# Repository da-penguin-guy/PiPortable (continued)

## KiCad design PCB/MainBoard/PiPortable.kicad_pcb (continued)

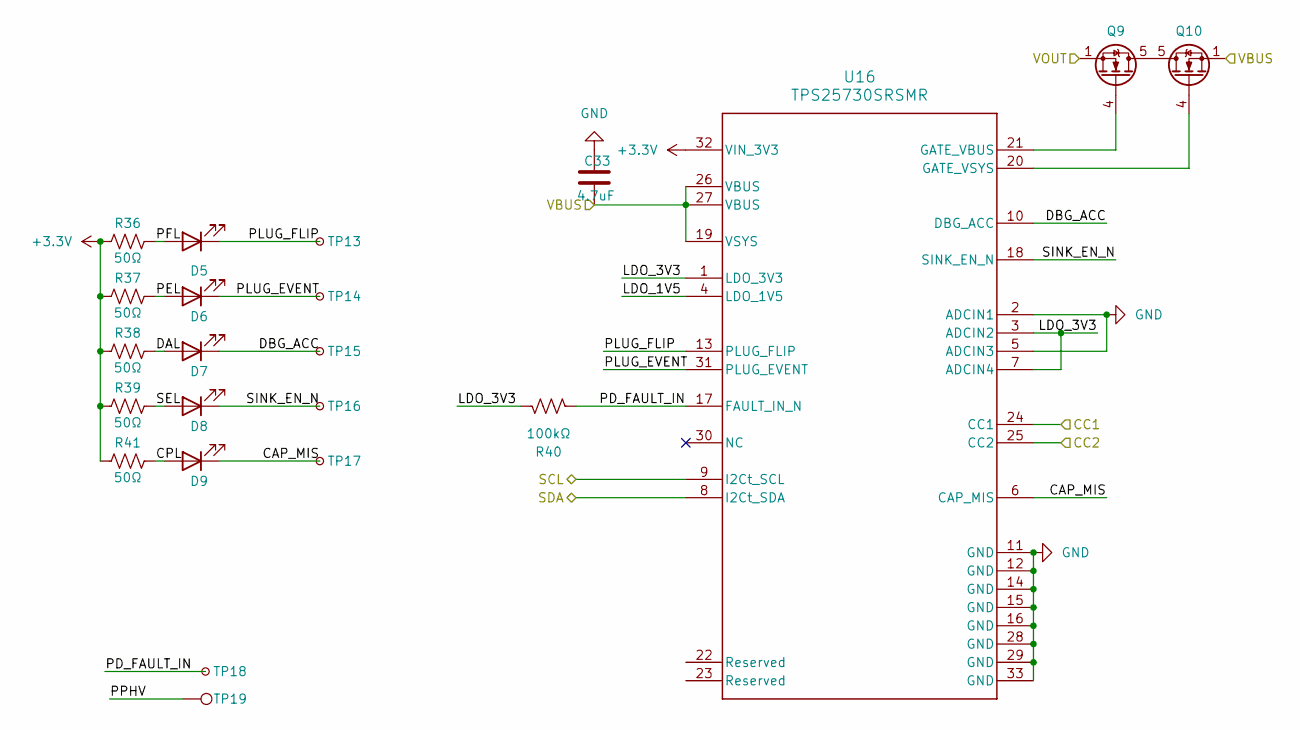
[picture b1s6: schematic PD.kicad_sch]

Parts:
C33: 4.7uF; C_0603_1608Metric_Pad1.08x0.95mm_HandSolder
D5, D6, D7, D8, D9: KT-0603R; LED_0603_1608Metric
Q9, Q10: CSD17577Q3A; VSON-8_3.3x3.3mm_P0.65mm_NexFET
R36, R37, R38, R39, R41: 50Ω; R_0402_1005Metric_Pad0.72x0.64mm_HandSolder
R40: 100kΩ; R_0402_1005Metric_Pad0.72x0.64mm_HandSolder
TP13, TP14, TP15, TP16, TP17, TP18: TestPoint_Small; TestPoint_Pad_D1.0mm
TP19: TestPoint; TestPoint_Pad_D3.0mm
U16: TPS25730SRSMR; RSM0032B-IPC_A

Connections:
+3.3V: R36.2, R37.2, R38.2, R39.2, R41.2, U16.32 (VIN_3V3); also elsewhere on the board
/PD Controller/CAP_MIS: D9.1 (K), TP17.1, U16.6 (CAP_MIS)
/PD Controller/CC1: U16.24 (CC1); also elsewhere on the board
/PD Controller/CC2: U16.25 (CC2); also elsewhere on the board
/PD Controller/CPL: D9.2 (A), R41.1
/PD Controller/DAL: D7.2 (A), R38.1
/PD Controller/DBG_ACC: D7.1 (K), TP15.1, U16.10 (DBG_ACC)
/PD Controller/LDO_1V5: U16.4 (LDO_1V5)
/PD Controller/LDO_3V3: R40.2, U16.1 (LDO_3V3), U16.3 (ADCIN2), U16.7 (ADCIN4)
/PD Controller/PD_FAULT_IN: R40.1, TP18.1, U16.17 (FAULT_IN_N)
/PD Controller/PEL: D6.2 (A), R37.1
/PD Controller/PFL: D5.2 (A), R36.1
/PD Controller/PLUG_EVENT: D6.1 (K), TP14.1, U16.31 (PLUG_EVENT)
/PD Controller/PLUG_FLIP: D5.1 (K), TP13.1, U16.13 (PLUG_FLIP)
/PD Controller/PPHV: TP19.1
/PD Controller/SEL: D8.2 (A), R39.1
/PD Controller/SINK_EN_N: D8.1 (K), TP16.1, U16.18 (SINK_EN_N)
/PD Controller/VOUT: Q9.1 (S), Q9.2 (S), Q9.3 (S); also elsewhere on the board
/SCL_INT: U16.9 (I2Ct_SCL); also elsewhere on the board
/SDA_INT: U16.8 (I2Ct_SDA); also elsewhere on the board
/VBUS: C33.2, Q10.1 (S), Q10.2 (S), Q10.3 (S), U16.19 (VSYS), U16.26 (VBUS), U16.27 (VBUS); also elsewhere on the board
GND: C33.1, U16.2 (ADCIN1), U16.5 (ADCIN3), U16.11 (GND), U16.12 (GND), U16.14 (GND), U16.15 (GND), U16.16 (GND), U16.28 (GND), U16.29 (GND), U16.33 (GND); also elsewhere on the board
unnamed: Q9.4 (G), U16.21 (GATE_VBUS)
unnamed: Q9.5 (D), Q10.5 (D)
unnamed: Q10.4 (G), U16.20 (GATE_VSYS)

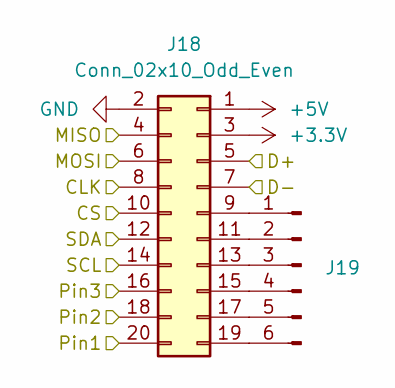
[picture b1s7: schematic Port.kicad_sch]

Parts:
J18: Conn_02x10_Odd_Even; PinSocket_2x10_P2.00mm_Horizontal
J19: Conn_01x06_Pin; PinHeader_1x06_P1.27mm_Vertical

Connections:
+3.3V: J18.3; also elsewhere on the board
+5V: J18.1; also elsewhere on the board
/CM5_GPIO ( Ethernet, GPIO, SDCARD)/GPIO9: J18.4; also elsewhere on the board
/CM5_GPIO ( Ethernet, GPIO, SDCARD)/GPIO10: J18.6; also elsewhere on the board
/CM5_GPIO ( Ethernet, GPIO, SDCARD)/GPIO11: J18.8; also elsewhere on the board
/CM5_GPIO ( Ethernet, GPIO, SDCARD)/GPIO22: J18.10; also elsewhere on the board
/IO Ports/Port1/D+: J18.5; also elsewhere on the board
/IO Ports/Port1/D-: J18.7; also elsewhere on the board
/IO Ports/Port1P1: J18.20; also elsewhere on the board
/IO Ports/Port1P2: J18.18; also elsewhere on the board
/IO Ports/Port1P3: J18.16; also elsewhere on the board
/SCL_GPIO: J18.14; also elsewhere on the board
/SDA_GPIO: J18.12; also elsewhere on the board
GND: J18.2; also elsewhere on the board
unnamed: J18.9, J19.1
unnamed: J18.11, J19.2
unnamed: J18.13, J19.3
unnamed: J18.15, J19.4
unnamed: J18.17, J19.5
unnamed: J18.19, J19.6

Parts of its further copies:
J20, J22, J24: Conn_02x10_Odd_Even; PinSocket_2x10_P2.00mm_Horizontal
J21, J23, J25: Conn_01x06_Pin; PinHeader_1x06_P1.27mm_Vertical

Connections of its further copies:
+3.3V: J20.3, J22.3, J24.3; also elsewhere on the board
+5V: J20.1, J22.1, J24.1; also elsewhere on the board
/CM5_GPIO ( Ethernet, GPIO, SDCARD)/GPIO9: J20.4, J22.4, J24.4; also elsewhere on the board
/CM5_GPIO ( Ethernet, GPIO, SDCARD)/GPIO10: J20.6, J22.6, J24.6; also elsewhere on the board
/CM5_GPIO ( Ethernet, GPIO, SDCARD)/GPIO11: J20.8, J22.8, J24.8; also elsewhere on the board
/CM5_GPIO ( Ethernet, GPIO, SDCARD)/GPIO23: J20.10; also elsewhere on the board
/CM5_GPIO ( Ethernet, GPIO, SDCARD)/GPIO24: J22.10; also elsewhere on the board
/CM5_GPIO ( Ethernet, GPIO, SDCARD)/GPIO25: J24.10; also elsewhere on the board
/IO Ports/Port2/D+: J20.5; also elsewhere on the board
/IO Ports/Port2/D-: J20.7; also elsewhere on the board
/IO Ports/Port2P1: J20.20; also elsewhere on the board
/IO Ports/Port2P2: J20.18; also elsewhere on the board
/IO Ports/Port2P3: J20.16; also elsewhere on the board
/IO Ports/Port3/D+: J22.5; also elsewhere on the board
/IO Ports/Port3/D-: J22.7; also elsewhere on the board
/IO Ports/Port3P1: J22.20; also elsewhere on the board
/IO Ports/Port3P2: J22.18; also elsewhere on the board
/IO Ports/Port3P3: J22.16; also elsewhere on the board
/IO Ports/Port4/D+: J24.5; also elsewhere on the board
/IO Ports/Port4/D-: J24.7; also elsewhere on the board
/IO Ports/Port4P1: J24.20; also elsewhere on the board
/IO Ports/Port4P2: J24.18; also elsewhere on the board
/IO Ports/Port4P3: J24.16; also elsewhere on the board
/SCL_GPIO: J20.14, J22.14, J24.14; also elsewhere on the board
/SDA_GPIO: J20.12, J22.12, J24.12; also elsewhere on the board
GND: J20.2, J22.2, J24.2; also elsewhere on the board
unnamed: J20.9, J21.1
unnamed: J20.11, J21.2
unnamed: J20.13, J21.3
unnamed: J20.15, J21.4
unnamed: J20.17, J21.5
unnamed: J20.19, J21.6
unnamed: J22.9, J23.1
unnamed: J22.11, J23.2
unnamed: J22.13, J23.3
unnamed: J22.15, J23.4
unnamed: J22.17, J23.5
unnamed: J22.19, J23.6
unnamed: J24.9, J25.1
unnamed: J24.11, J25.2
unnamed: J24.13, J25.3
unnamed: J24.15, J25.4
unnamed: J24.17, J25.5
unnamed: J24.19, J25.6

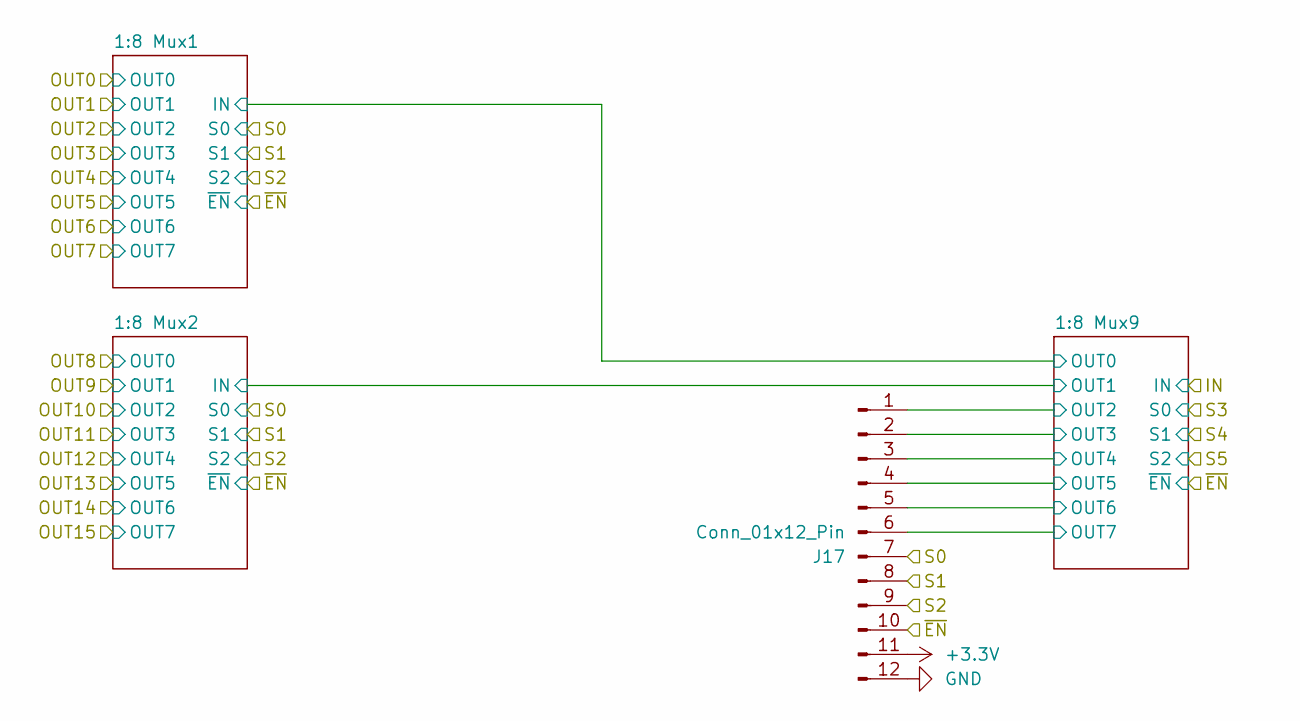
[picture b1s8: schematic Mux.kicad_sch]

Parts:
J17: Conn_01x12_Pin; PinHeader_1x12_P1.27mm_Vertical

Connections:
+3.3V: J17.11; also elsewhere on the board
/IO Ports/Mux 2/1:8 Mux9/OUT2: J17.1; also elsewhere on the board
/IO Ports/Mux 2/1:8 Mux9/OUT3: J17.2; also elsewhere on the board
/IO Ports/Mux 2/1:8 Mux9/OUT4: J17.3; also elsewhere on the board
/IO Ports/Mux 2/1:8 Mux9/OUT5: J17.4; also elsewhere on the board
/IO Ports/Mux 2/1:8 Mux9/OUT6: J17.5; also elsewhere on the board
/IO Ports/Mux 2/1:8 Mux9/OUT7: J17.6; also elsewhere on the board
/IO Ports/Mux 2/S0: J17.7; also elsewhere on the board
/IO Ports/Mux 2/S1: J17.8; also elsewhere on the board
/IO Ports/Mux 2/S2: J17.9; also elsewhere on the board
/IO Ports/Mux 2/~EN: J17.10; also elsewhere on the board
GND: J17.12; also elsewhere on the board

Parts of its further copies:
J16: Conn_01x12_Pin; PinHeader_1x12_P1.27mm_Vertical

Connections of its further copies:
+3.3V: J16.11; also elsewhere on the board
/IO Ports/Mux 1/1:8 Mux9/OUT2: J16.1; also elsewhere on the board
/IO Ports/Mux 1/1:8 Mux9/OUT3: J16.2; also elsewhere on the board
/IO Ports/Mux 1/1:8 Mux9/OUT4: J16.3; also elsewhere on the board
/IO Ports/Mux 1/1:8 Mux9/OUT5: J16.4; also elsewhere on the board
/IO Ports/Mux 1/1:8 Mux9/OUT6: J16.5; also elsewhere on the board
/IO Ports/Mux 1/1:8 Mux9/OUT7: J16.6; also elsewhere on the board
/IO Ports/Mux 1/S0: J16.7; also elsewhere on the board
/IO Ports/Mux 1/S1: J16.8; also elsewhere on the board
/IO Ports/Mux 1/S2: J16.9; also elsewhere on the board
/IO Ports/Mux 1/~EN: J16.10; also elsewhere on the board
GND: J16.12; also elsewhere on the board

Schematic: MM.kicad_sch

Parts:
J15: Conn_01x02_Pin; PinHeader_1x02_P1.27mm_Vertical
Q1, Q2: 2N7002; SOT-23
R7: 50Ω; R_0402_1005Metric_Pad0.72x0.64mm_HandSolder
U4: PINA780BIDEKR; VQFN15_DEK_TEX

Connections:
+3.3V: Q1.2 (S), U4.15 (IS+); also elsewhere on the board
/IO Ports/Multimeter/3.3EN: Q1.1 (G); also elsewhere on the board
/IO Ports/Multimeter/GNDEN: Q2.1 (G); also elsewhere on the board
/IO Ports/VS+: J15.1, R7.2, U4.6 (SCL), U4.7 (NC); also elsewhere on the board
/IO Ports/VS-: Q2.3 (D); also elsewhere on the board
/SCL_GPIO: U4.10 (IN-); also elsewhere on the board
/SDA_GPIO: U4.11 (ALERT); also elsewhere on the board
GND: Q2.2 (S); also elsewhere on the board
unnamed: J15.2, Q1.3 (D), R7.1

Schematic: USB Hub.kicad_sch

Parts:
R8: 12kΩ; R_0402_1005Metric_Pad0.72x0.64mm_HandSolder
TP2, TP3, TP4, TP5: TestPoint_Small; TestPoint_Pad_D1.0mm
U5: USB2514B_Bi; QFN-36-1EP_6x6mm_P0.5mm_EP3.7x3.7mm
Y1: ABM8-24.000MHZ-D1G-T; Crystal_SMD_Abracon_ABM8G-4Pin_3.2x2.5mm

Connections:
+3.3V: U5.5 (VDDA33), U5.10 (VDDA33), U5.15 (VDD33), U5.23 (VDD33), U5.26 (RESET_N), U5.27 (VBUS_DET), U5.29 (VDDA33), U5.36 (VDDA33); also elsewhere on the board
/CM5_HighSpeed/USB3-1-D_N: U5.30 (USBDM_UP); also elsewhere on the board
/CM5_HighSpeed/USB3-1-D_P: U5.31 (USBDP_UP); also elsewhere on the board
/IO Ports/Port1/D+: U5.2 (USBDP_DN1/PRT_DIS_P1); also elsewhere on the board
/IO Ports/Port1/D-: U5.1 (USBDM_DN1/PRT_DIS_M1); also elsewhere on the board
/IO Ports/Port2/D+: U5.4 (USBDP_DN2/PRT_DIS_P2); also elsewhere on the board
/IO Ports/Port2/D-: U5.3 (USBDM_DN2/PRT_DIS_M2); also elsewhere on the board
/IO Ports/Port3/D+: U5.7 (USBDP_DN3/PRT_DIS_P3); also elsewhere on the board
/IO Ports/Port3/D-: U5.6 (USBDM_DN3/PRT_DIS_M3); also elsewhere on the board
/IO Ports/Port4/D+: U5.9 (USBDP_DN4/PRT_DIS_P4); also elsewhere on the board
/IO Ports/Port4/D-: U5.8 (USBDM_DN4/PRT_DIS_M4); also elsewhere on the board
/SCL_GPIO: U5.24 (SCL/SMBCLK/CFG_SEL0); also elsewhere on the board
/SDA_GPIO: U5.22 (SDA/SMBDATA/NON_REM1); also elsewhere on the board
GND: R8.1, U5.12 (PRTPWR1/BC_EN1), U5.16 (PRTPWR2/BC_EN2), U5.18 (PRTPWR3/BC_EN3), U5.20 (PRTPWR4/BC_EN4), U5.37 (VSS), Y1.2, Y1.4; also elsewhere on the board
unnamed: TP2.1, U5.13 (OCS_N1)
unnamed: TP3.1, U5.17 (OCS_N2)
unnamed: TP4.1, U5.19 (OCS_N3)
unnamed: TP5.1, U5.21 (OCS_N4)
unnamed: R8.2, U5.35 (RBIAS)
unnamed: U5.33 (XTALIN/CLKIN), Y1.1
unnamed: U5.32 (XTALOUT), Y1.3

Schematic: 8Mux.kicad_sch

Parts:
U10: 74HC4051; TSSOP-16_4.4x5mm_P0.65mm

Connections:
+3.3V: U10.16 (VCC); also elsewhere on the board
/IO Ports/L12: U10.1 (A4); also elsewhere on the board
/IO Ports/L13: U10.5 (A5); also elsewhere on the board
/IO Ports/L14: U10.2 (A6); also elsewhere on the board
/IO Ports/L15: U10.4 (A7); also elsewhere on the board
/IO Ports/Mux 2/1:8 Mux2/IN: U10.3 (A); also elsewhere on the board
/IO Ports/Mux 2/S0: U10.11 (S0); also elsewhere on the board
/IO Ports/Mux 2/S1: U10.10 (S1); also elsewhere on the board
/IO Ports/Mux 2/S2: U10.9 (S2); also elsewhere on the board
/IO Ports/Mux 2/~EN: U10.6 (~E); also elsewhere on the board
/IO Ports/Port3P3: U10.13 (A0); also elsewhere on the board
/IO Ports/Port4P1: U10.14 (A1); also elsewhere on the board
/IO Ports/Port4P2: U10.15 (A2); also elsewhere on the board
/IO Ports/Port4P3: U10.12 (A3); also elsewhere on the board
GND: U10.7 (VEE), U10.8 (GND); also elsewhere on the board

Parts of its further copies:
U7, U8, U9, U11, U13: 74HC4051; TSSOP-16_4.4x5mm_P0.65mm

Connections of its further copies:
+3.3V: U7.16 (VCC), U8.16 (VCC), U9.16 (VCC), U11.16 (VCC), U13.16 (VCC); also elsewhere on the board
/IO Ports/H12: U7.1 (A4); also elsewhere on the board
/IO Ports/H13: U7.5 (A5); also elsewhere on the board
/IO Ports/H14: U7.2 (A6); also elsewhere on the board
/IO Ports/H15: U7.4 (A7); also elsewhere on the board
/IO Ports/Mux 1/1:8 Mux1/IN: U8.3 (A), U13.13 (A0)
/IO Ports/Mux 1/1:8 Mux2/IN: U7.3 (A), U13.14 (A1)
/IO Ports/Mux 1/1:8 Mux9/OUT2: U13.15 (A2); also elsewhere on the board
/IO Ports/Mux 1/1:8 Mux9/OUT3: U13.12 (A3); also elsewhere on the board
/IO Ports/Mux 1/1:8 Mux9/OUT4: U13.1 (A4); also elsewhere on the board
/IO Ports/Mux 1/1:8 Mux9/OUT5: U13.5 (A5); also elsewhere on the board
/IO Ports/Mux 1/1:8 Mux9/OUT6: U13.2 (A6); also elsewhere on the board
/IO Ports/Mux 1/1:8 Mux9/OUT7: U13.4 (A7); also elsewhere on the board
/IO Ports/Mux 1/S0: U7.11 (S0), U8.11 (S0); also elsewhere on the board
/IO Ports/Mux 1/S1: U7.10 (S1), U8.10 (S1); also elsewhere on the board
/IO Ports/Mux 1/S2: U7.9 (S2), U8.9 (S2); also elsewhere on the board
/IO Ports/Mux 1/S3: U13.11 (S0); also elsewhere on the board
/IO Ports/Mux 1/S4: U13.10 (S1); also elsewhere on the board
/IO Ports/Mux 1/S5: U13.9 (S2); also elsewhere on the board
/IO Ports/Mux 1/~EN: U7.6 (~E), U8.6 (~E), U13.6 (~E); also elsewhere on the board
/IO Ports/Mux 2/1:8 Mux1/IN: U9.13 (A0), U11.3 (A)
/IO Ports/Mux 2/1:8 Mux2/IN: U9.14 (A1); also elsewhere on the board
/IO Ports/Mux 2/1:8 Mux9/OUT2: U9.15 (A2); also elsewhere on the board
/IO Ports/Mux 2/1:8 Mux9/OUT3: U9.12 (A3); also elsewhere on the board
/IO Ports/Mux 2/1:8 Mux9/OUT4: U9.1 (A4); also elsewhere on the board
/IO Ports/Mux 2/1:8 Mux9/OUT5: U9.5 (A5); also elsewhere on the board
/IO Ports/Mux 2/1:8 Mux9/OUT6: U9.2 (A6); also elsewhere on the board
/IO Ports/Mux 2/1:8 Mux9/OUT7: U9.4 (A7); also elsewhere on the board
/IO Ports/Mux 2/S0: U11.11 (S0); also elsewhere on the board
/IO Ports/Mux 2/S1: U11.10 (S1); also elsewhere on the board
/IO Ports/Mux 2/S2: U11.9 (S2); also elsewhere on the board
/IO Ports/Mux 2/S3: U9.11 (S0); also elsewhere on the board
/IO Ports/Mux 2/S4: U9.10 (S1); also elsewhere on the board
/IO Ports/Mux 2/S5: U9.9 (S2); also elsewhere on the board
/IO Ports/Mux 2/~EN: U9.6 (~E), U11.6 (~E); also elsewhere on the board
/IO Ports/Port1P1: U8.13 (A0), U11.13 (A0); also elsewhere on the board
/IO Ports/Port1P2: U8.14 (A1), U11.14 (A1); also elsewhere on the board
/IO Ports/Port1P3: U8.15 (A2), U11.15 (A2); also elsewhere on the board
/IO Ports/Port2P1: U8.12 (A3), U11.12 (A3); also elsewhere on the board
/IO Ports/Port2P2: U8.1 (A4), U11.1 (A4); also elsewhere on the board
/IO Ports/Port2P3: U8.5 (A5), U11.5 (A5); also elsewhere on the board
/IO Ports/Port3P1: U8.2 (A6), U11.2 (A6); also elsewhere on the board
/IO Ports/Port3P2: U8.4 (A7), U11.4 (A7); also elsewhere on the board
/IO Ports/Port3P3: U7.13 (A0); also elsewhere on the board
/IO Ports/Port4P1: U7.14 (A1); also elsewhere on the board
/IO Ports/Port4P2: U7.15 (A2); also elsewhere on the board
/IO Ports/Port4P3: U7.12 (A3); also elsewhere on the board
/IO Ports/VS+: U13.3 (A); also elsewhere on the board
/IO Ports/VS-: U9.3 (A); also elsewhere on the board
GND: U7.7 (VEE), U7.8 (GND), U8.7 (VEE), U8.8 (GND), U9.7 (VEE), U9.8 (GND), U11.7 (VEE), U11.8 (GND), U13.7 (VEE), U13.8 (GND); also elsewhere on the board

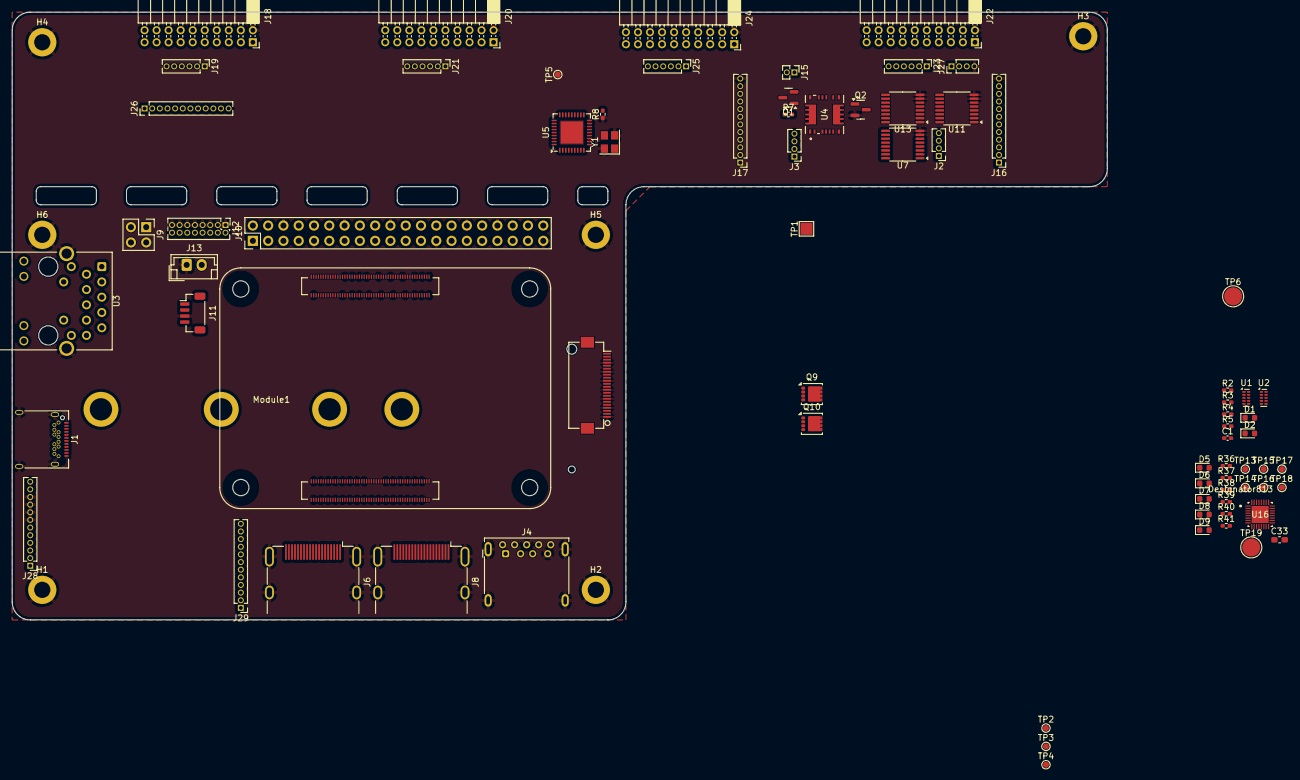
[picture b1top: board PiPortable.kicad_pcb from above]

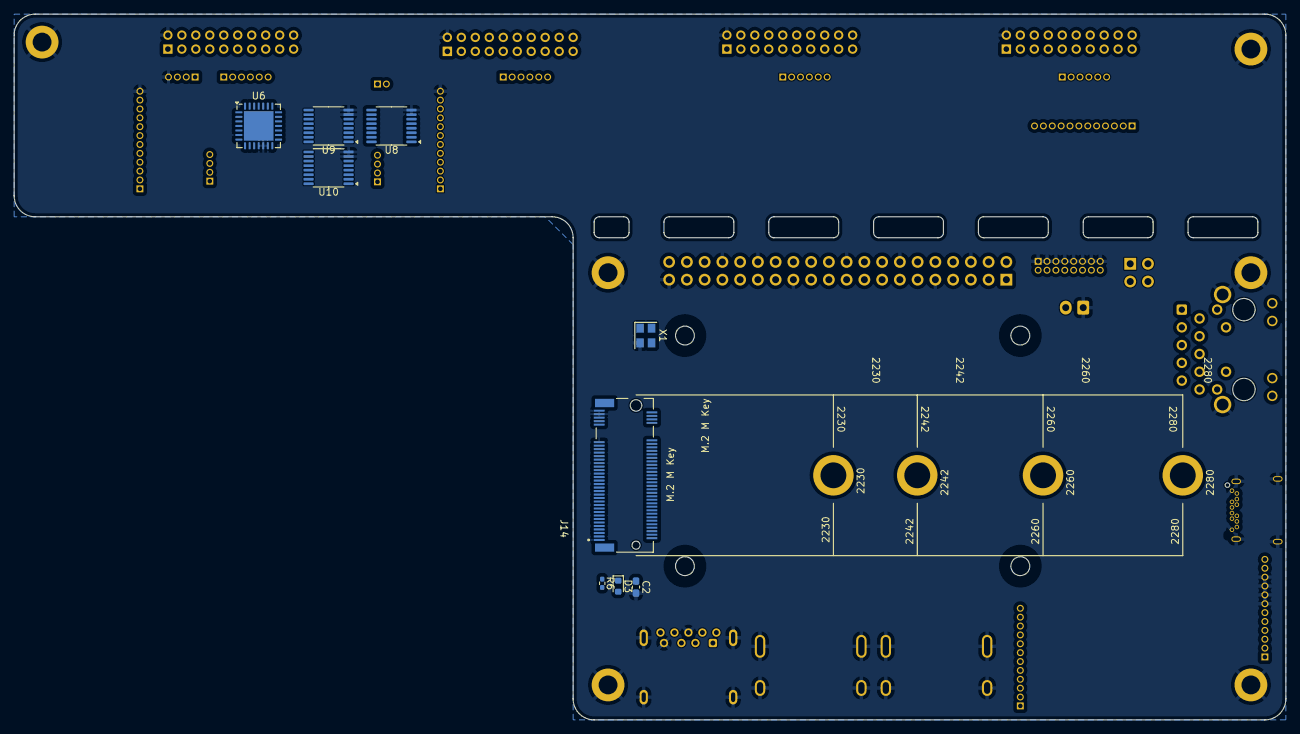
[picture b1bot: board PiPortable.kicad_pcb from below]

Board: 6 copper layers, 182.0 x 101.0 mm, 91 parts (9 on the bottom side), 238 nets.

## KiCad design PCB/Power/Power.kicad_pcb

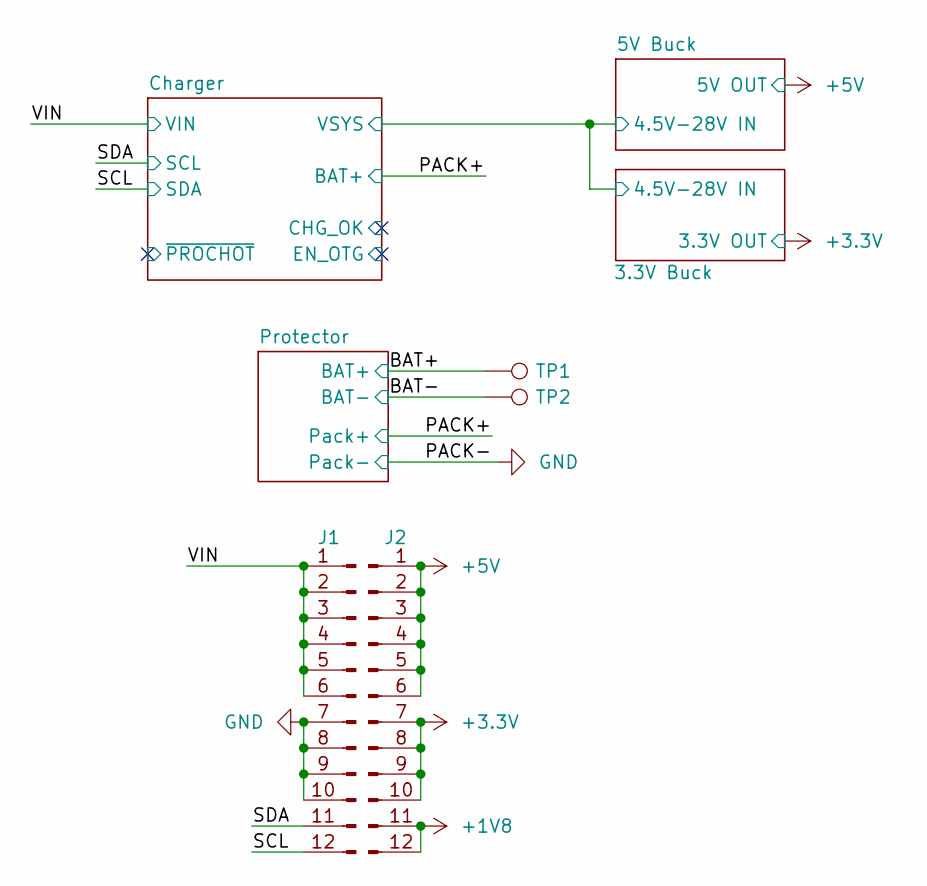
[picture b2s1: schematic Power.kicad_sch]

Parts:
J1, J2: Conn_01x12_Pin; PinSocket_1x12_P1.27mm_Vertical
TP1, TP2: TestPoint; TestPoint_THTPad_D3.0mm_Drill1.5mm

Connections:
+1V8: J2.11, J2.12
+3.3V: J2.7, J2.8, J2.9, J2.10; also elsewhere on the board
+5V: J2.1, J2.2, J2.3, J2.4, J2.5, J2.6; also elsewhere on the board
/BAT+: TP1.1; also elsewhere on the board
/BAT-: TP2.1; also elsewhere on the board
/SCL: J1.12; also elsewhere on the board
/SDA: J1.11; also elsewhere on the board
/VIN: J1.1, J1.2, J1.3, J1.4, J1.5, J1.6; also elsewhere on the board
GND: J1.7, J1.8, J1.9, J1.10; also elsewhere on the board

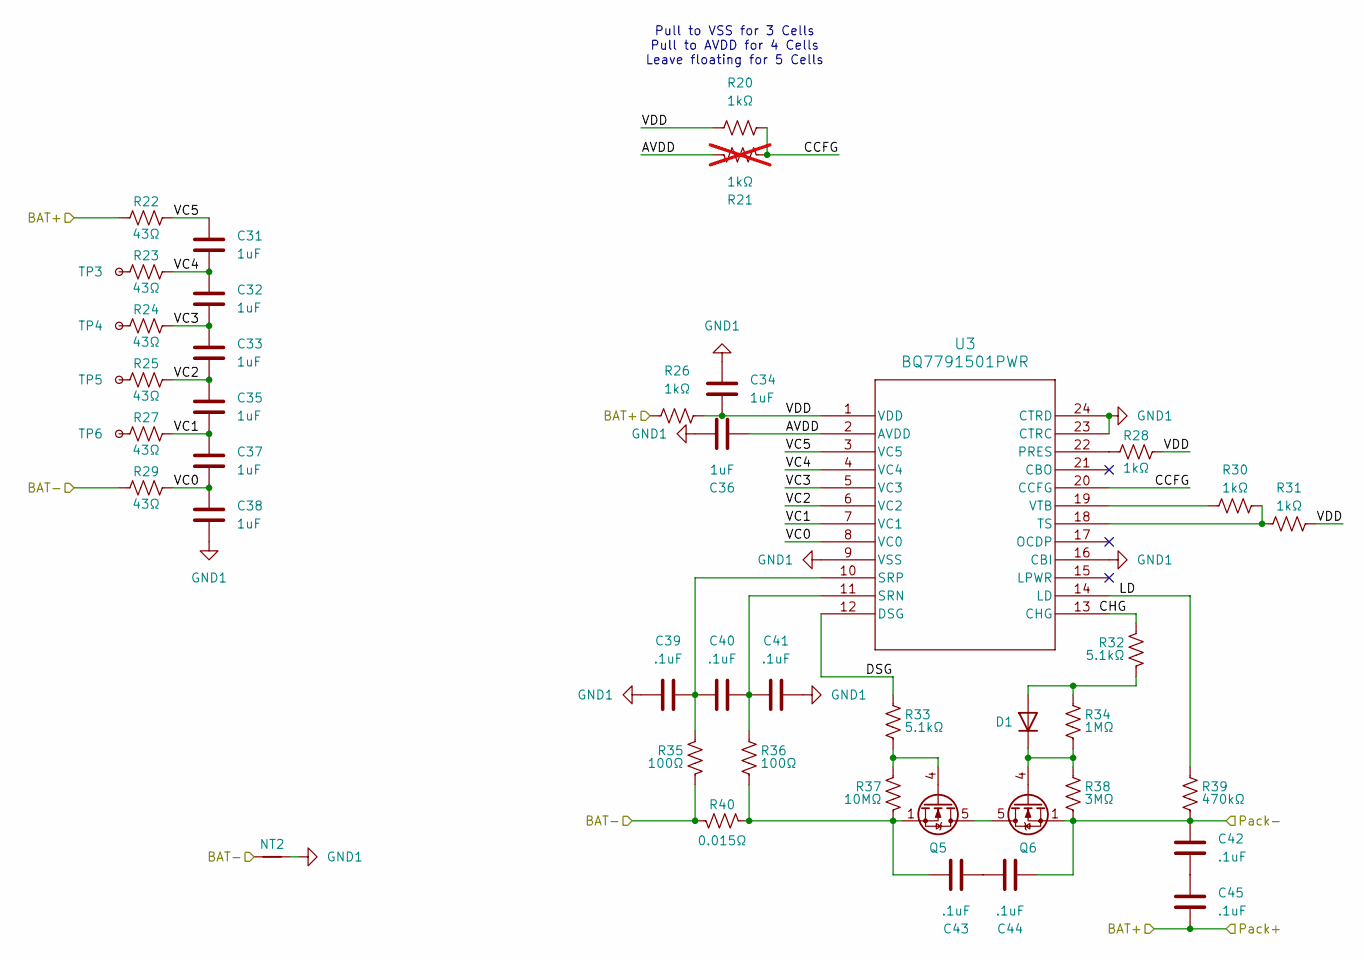
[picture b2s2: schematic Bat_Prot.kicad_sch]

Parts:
C31, C32, C33, C34, C35, C36, C37, C38: 1uF; C_0402_1005Metric_Pad0.74x0.62mm_HandSolder
C39, C40, C41, C42, C43, C44, C45: .1uF; C_0402_1005Metric_Pad0.74x0.62mm_HandSolder
D1: BAS16J,135; D_SOD-323F
NT2: NetTie_2; NetTie-2_SMD_Pad2.0mm
Q5, Q6: CSD17577Q3A; VSON-8_3.3x3.3mm_P0.65mm_NexFET
R20, R26, R28, R30, R31: 1kΩ; R_0402_1005Metric_Pad0.72x0.64mm_HandSolder
R21: 1kΩ; R_0402_1005Metric_Pad0.72x0.64mm_HandSolder; not fitted
R22, R23, R24, R25, R27, R29: 43Ω; R_0402_1005Metric_Pad0.72x0.64mm_HandSolder
R32, R33: 5.1kΩ; R_0402_1005Metric_Pad0.72x0.64mm_HandSolder
R34: 1MΩ; R_0603_1608Metric_Pad0.98x0.95mm_HandSolder
R35, R36: 100Ω; R_0402_1005Metric_Pad0.72x0.64mm_HandSolder
R37: 10MΩ; R_0603_1608Metric_Pad0.98x0.95mm_HandSolder
R38: 3MΩ; R_0603_1608Metric_Pad0.98x0.95mm_HandSolder
R39: 470kΩ; R_0402_1005Metric_Pad0.72x0.64mm_HandSolder
R40: 0.015Ω; R_0805_2012Metric_Pad1.20x1.40mm_HandSolder
TP3, TP4, TP5, TP6: TestPoint_Small; TestPoint_Pad_D1.0mm
U3: BQ7791501PWR; PW24_TEX

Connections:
/BAT+: C45.2, R22.1, R26.1; also elsewhere on the board
/BAT-: NT2.1, R29.1, R35.2, R40.2; also elsewhere on the board
/Protector/AVDD: C36.2, R21.2, U3.2 (AVDD)
/Protector/CCFG: R20.2, R21.1, U3.20 (CCFG)
/Protector/CHG: R32.1, U3.13 (CHG)
/Protector/DSG: R33.1, U3.12 (DSG)
/Protector/LD: R39.1, U3.14 (LD)
/Protector/VC0: C37.2, C38.1, R29.2, U3.8 (VC0)
/Protector/VC1: C35.2, C37.1, R27.2, U3.7 (VC1)
/Protector/VC2: C33.2, C35.1, R25.2, U3.6 (VC2)
/Protector/VC3: C32.2, C33.1, R24.2, U3.5 (VC3)
/Protector/VC4: C31.2, C32.1, R23.2, U3.4 (VC4)
/Protector/VC5: C31.1, R22.2, U3.3 (VC5)
/Protector/VDD: C34.2, R20.1, R26.2, R28.2, R31.2, U3.1 (VDD)
GND: C42.1, C44.2, Q6.1 (S), Q6.2 (S), Q6.3 (S), R38.2, R39.2; also elsewhere on the board
GND1: C34.1, C36.1, C38.2, C39.2, C41.2, NT2.2, U3.9 (VSS), U3.16 (CBI), U3.23 (CTRC), U3.24 (CTRD)
unnamed: C42.2, C45.1
unnamed: C43.1, Q5.1 (S), Q5.2 (S), Q5.3 (S), R36.2, R37.2, R40.1
unnamed: C43.2, C44.1
unnamed: D1.2 (A), R32.2, R34.1
unnamed: D1.1 (K), Q6.4 (G), R34.2, R38.1
unnamed: Q5.5 (D), Q6.5 (D)
unnamed: Q5.4 (G), R33.2, R37.1
unnamed: R23.1, TP3.1
unnamed: R24.1, TP4.1
unnamed: R25.1, TP5.1
unnamed: R27.1, TP6.1
unnamed: R28.1, U3.22 (PRES)
unnamed: C40.2, C41.1, R36.1, U3.11 (SRN)
unnamed: C39.1, C40.1, R35.1, U3.10 (SRP)
unnamed: R30.2, R31.1, U3.18 (TS)
unnamed: R30.1, U3.19 (VTB)

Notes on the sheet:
Pull to VSS for 3 Cells Pull to AVDD for 4 Cells Leave floating for 5 Cells

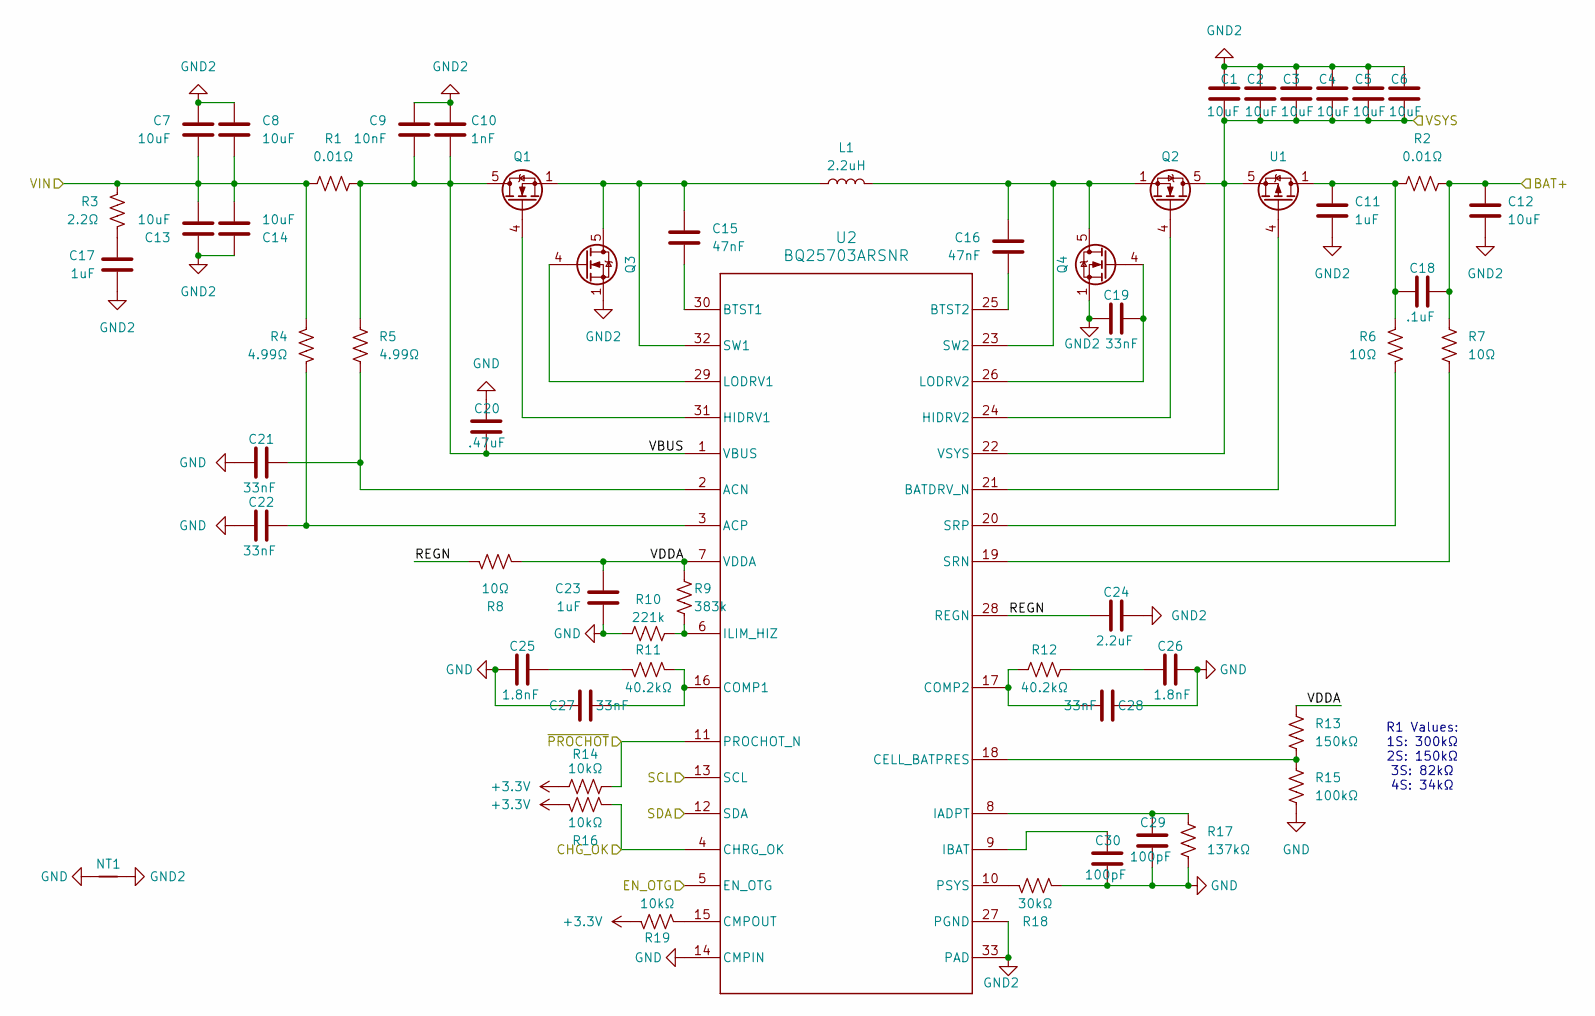
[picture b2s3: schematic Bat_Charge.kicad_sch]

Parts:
C1, C2, C3, C4, C7, C8, C12, C13, C14: 10uF; C_0603_1608Metric_Pad1.08x0.95mm_HandSolder
C5, C6: 10uF; C_0402_1005Metric_Pad0.74x0.62mm_HandSolder
C9: 10nF; C_0402_1005Metric_Pad0.74x0.62mm_HandSolder
C10: 1nF; C_0402_1005Metric_Pad0.74x0.62mm_HandSolder
C11: 1uF; C_0603_1608Metric_Pad1.08x0.95mm_HandSolder
C15, C16: 47nF; C_0402_1005Metric_Pad0.74x0.62mm_HandSolder
C17, C23: 1uF; C_0402_1005Metric_Pad0.74x0.62mm_HandSolder
C18: .1uF; C_0603_1608Metric_Pad1.08x0.95mm_HandSolder
C19, C21, C22, C27, C28: 33nF; C_0402_1005Metric_Pad0.74x0.62mm_HandSolder
C20: .47uF; C_0402_1005Metric_Pad0.74x0.62mm_HandSolder
C24: 2.2uF; C_0603_1608Metric_Pad1.08x0.95mm_HandSolder
C25, C26: 1.8nF; C_0402_1005Metric_Pad0.74x0.62mm_HandSolder
C29, C30: 100pF; C_0402_1005Metric_Pad0.74x0.62mm_HandSolder
L1: 2.2uH; L_Coilcraft_XAL7030-222
NT1: NetTie_2; NetTie-2_SMD_Pad2.0mm
Q1, Q2, Q3, Q4: CSD17577Q3A; VSON-8_3.3x3.3mm_P0.65mm_NexFET
R1, R2: 0.01Ω; R_0805_2012Metric_Pad1.20x1.40mm_HandSolder
R3: 2.2Ω; R_0402_1005Metric_Pad0.72x0.64mm_HandSolder
R4, R5: 4.99Ω; R_0402_1005Metric_Pad0.72x0.64mm_HandSolder
R6, R7, R8: 10Ω; R_0402_1005Metric_Pad0.72x0.64mm_HandSolder
R9: 383k; R_0402_1005Metric_Pad0.72x0.64mm_HandSolder
R10: 221k; R_0402_1005Metric_Pad0.72x0.64mm_HandSolder
R11, R12: 40.2kΩ; R_0402_1005Metric_Pad0.72x0.64mm_HandSolder
R13: 150kΩ; R_0402_1005Metric_Pad0.72x0.64mm_HandSolder
R14, R16, R19: 10kΩ; R_0402_1005Metric_Pad0.72x0.64mm_HandSolder
R15: 100kΩ; R_0402_1005Metric_Pad0.72x0.64mm_HandSolder
R17: 137kΩ; R_0402_1005Metric_Pad0.72x0.64mm_HandSolder
R18: 30kΩ; R_0402_1005Metric_Pad0.72x0.64mm_HandSolder
U1: CSD25402Q3A; VSON-8_3.3x3.3mm_P0.65mm_NexFET
U2: BQ25703ARSNR; RSN0032B

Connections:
+3.3V: R14.1, R16.1, R19.1; also elsewhere on the board
/3.3V Buck/4.5V-28V IN: C1.2, C2.2, C3.2, C4.2, C5.2, C6.2, Q2.5 (D), U1.5 (S), U2.22 (VSYS); also elsewhere on the board
/BAT+: C12.1, C18.2, R2.2, R7.1; also elsewhere on the board
/Charger/CHG_OK: R16.2, U2.4 (CHRG_OK)
/Charger/EN_OTG: U2.5 (EN_OTG)
/Charger/REGN: C24.1, R8.1, U2.28 (REGN)
/Charger/VBUS: C9.2, C10.2, C20.2, Q1.5 (D), R1.2, R5.1, U2.1 (VBUS)
/Charger/VDDA: C23.1, R8.2, R9.1, R13.1, U2.7 (VDDA)
/Charger/~PROCHOT: R14.2, U2.11 (PROCHOT_N)
/SCL: U2.12 (SDA); also elsewhere on the board
/SDA: U2.13 (SCL); also elsewhere on the board
/VIN: C7.2, C8.2, C13.2, C14.2, R1.1, R3.1, R4.1; also elsewhere on the board
GND: C20.1, C21.1, C22.1, C23.2, C25.1, C26.1, C27.1, C28.1, C29.2, C30.2, NT1.1, R10.1, R15.2, R17.2, R18.2, U2.14 (CMPIN); also elsewhere on the board
GND2: C1.1, C2.1, C3.1, C4.1, C5.1, C6.1, C7.1, C8.1, C9.1, C10.1, C11.2, C12.2, C13.1, C14.1, C17.2, C19.1, C24.2, NT1.2, Q3.1 (S), Q3.2 (S), Q3.3 (S), Q4.1 (S), Q4.2 (S), Q4.3 (S), U2.27 (PGND), U2.33 (PAD)
unnamed: C11.1, C18.1, R2.1, R6.1, U1.1 (D), U1.2 (D), U1.3 (D)
unnamed: C17.1, R3.2
unnamed: C25.2, R11.1
unnamed: C26.2, R12.1
unnamed: Q1.4 (G), U2.31 (HIDRV1)
unnamed: Q2.4 (G), U2.24 (HIDRV2)
unnamed: C15.1, L1.1, Q1.1 (S), Q1.2 (S), Q1.3 (S), Q3.5 (D), U2.32 (SW1)
unnamed: Q3.4 (G), U2.29 (LODRV1)
unnamed: C16.1, L1.2, Q2.1 (S), Q2.2 (S), Q2.3 (S), Q4.5 (D), U2.23 (SW2)
unnamed: C19.2, Q4.4 (G), U2.26 (LODRV2)
unnamed: U1.4 (G), U2.21 (BATDRV_N)
unnamed: C21.2, R5.2, U2.2 (ACN)
unnamed: C22.2, R4.2, U2.3 (ACP)
unnamed: C15.2, U2.30 (BTST1)
unnamed: C16.2, U2.25 (BTST2)
unnamed: R13.2, R15.1, U2.18 (CELL_BATPRES)
unnamed: R19.2, U2.15 (CMPOUT)
unnamed: C27.2, R11.2, U2.16 (COMP1)
unnamed: C28.2, R12.2, U2.17 (COMP2)
unnamed: C29.1, R17.1, U2.8 (IADPT)
unnamed: C30.1, U2.9 (IBAT)
unnamed: R9.2, R10.2, U2.6 (ILIM_HIZ)
unnamed: R18.1, U2.10 (PSYS)
unnamed: R7.2, U2.19 (SRN)
unnamed: R6.2, U2.20 (SRP)

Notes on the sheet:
R1 Values: 1S: 300kΩ 2S: 150kΩ 3S: 82kΩ 4S: 34kΩ

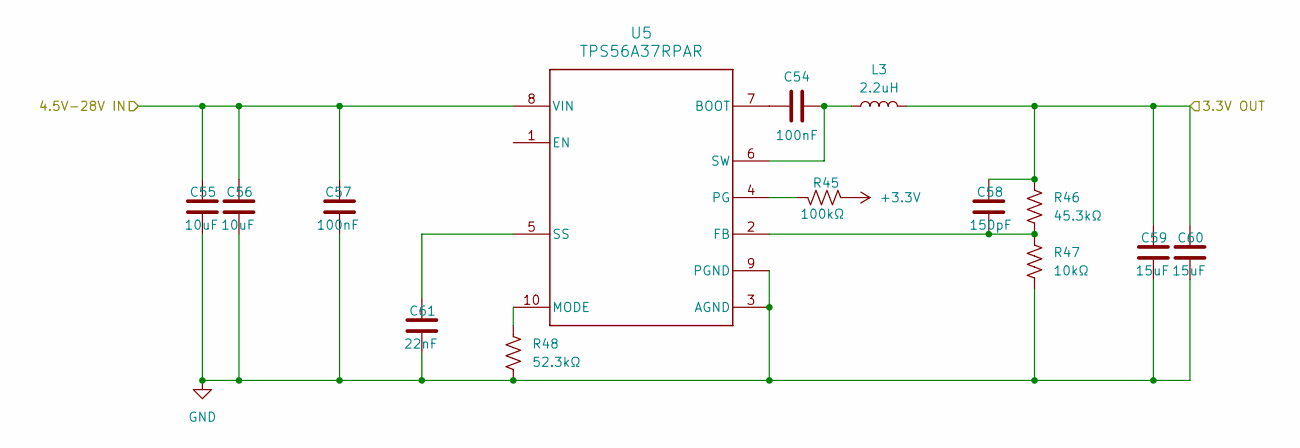
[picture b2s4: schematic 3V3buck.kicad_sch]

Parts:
C54, C57: 100nF; C_0402_1005Metric_Pad0.74x0.62mm_HandSolder
C55, C56: 10uF; C_0603_1608Metric_Pad1.08x0.95mm_HandSolder
C58: 150pF; C_0603_1608Metric_Pad1.08x0.95mm_HandSolder
C59, C60: 15uF; C_0603_1608Metric_Pad1.08x0.95mm_HandSolder
C61: 22nF; C_0402_1005Metric_Pad0.74x0.62mm_HandSolder
L3: 2.2uH; L_Coilcraft_XAL7030-222
R45: 100kΩ; R_0402_1005Metric_Pad0.72x0.64mm_HandSolder
R46: 45.3kΩ; R_0402_1005Metric_Pad0.72x0.64mm_HandSolder
R47: 10kΩ; R_0402_1005Metric_Pad0.72x0.64mm_HandSolder
R48: 52.3kΩ; R_0402_1005Metric_Pad0.72x0.64mm_HandSolder
U5: TPS56A37RPAR; RPA0010A-MFG

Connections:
+3.3V: C58.2, C59.2, C60.2, L3.2, R45.1, R46.1; also elsewhere on the board
/3.3V Buck/4.5V-28V IN: C55.2, C56.2, C57.2, U5.8 (VIN); also elsewhere on the board
GND: C55.1, C56.1, C57.1, C59.1, C60.1, C61.1, R47.2, R48.2, U5.3 (AGND), U5.9 (PGND); also elsewhere on the board
unnamed: C54.1, U5.7 (BOOT)
unnamed: C58.1, R46.2, R47.1, U5.2 (FB)
unnamed: R48.1, U5.10 (MODE)
unnamed: R45.2, U5.4 (PG)
unnamed: C61.2, U5.5 (SS)
unnamed: C54.2, L3.1, U5.6 (SW)

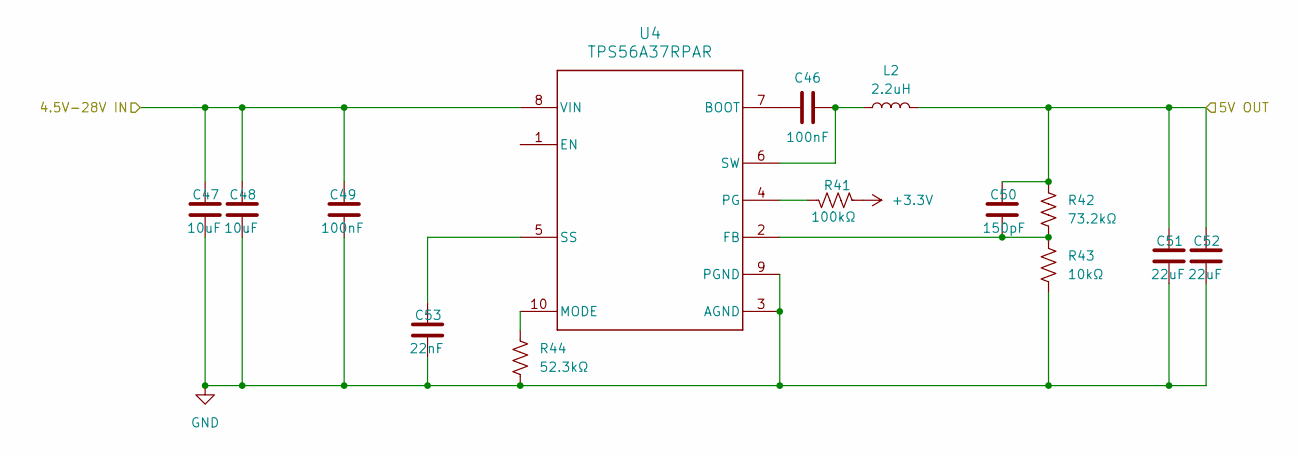
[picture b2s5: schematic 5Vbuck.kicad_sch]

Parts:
C46, C49: 100nF; C_0402_1005Metric_Pad0.74x0.62mm_HandSolder
C47, C48: 10uF; C_0603_1608Metric_Pad1.08x0.95mm_HandSolder
C50: 150pF; C_0603_1608Metric_Pad1.08x0.95mm_HandSolder
C51, C52: 22uF; C_0603_1608Metric_Pad1.08x0.95mm_HandSolder
C53: 22nF; C_0402_1005Metric_Pad0.74x0.62mm_HandSolder
L2: 2.2uH; L_Coilcraft_XAL7030-222
R41: 100kΩ; R_0402_1005Metric_Pad0.72x0.64mm_HandSolder
R42: 73.2kΩ; R_0402_1005Metric_Pad0.72x0.64mm_HandSolder
R43: 10kΩ; R_0402_1005Metric_Pad0.72x0.64mm_HandSolder
R44: 52.3kΩ; R_0402_1005Metric_Pad0.72x0.64mm_HandSolder
U4: TPS56A37RPAR; RPA0010A-MFG

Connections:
+3.3V: R41.1; also elsewhere on the board
+5V: C50.2, C51.2, C52.2, L2.2, R42.1; also elsewhere on the board
/3.3V Buck/4.5V-28V IN: C47.2, C48.2, C49.2, U4.8 (VIN); also elsewhere on the board
GND: C47.1, C48.1, C49.1, C51.1, C52.1, C53.1, R43.2, R44.2, U4.3 (AGND), U4.9 (PGND); also elsewhere on the board
unnamed: C46.1, U4.7 (BOOT)
unnamed: C50.1, R42.2, R43.1, U4.2 (FB)
unnamed: R44.1, U4.10 (MODE)
unnamed: R41.2, U4.4 (PG)
unnamed: C53.2, U4.5 (SS)
unnamed: C46.2, L2.1, U4.6 (SW)
